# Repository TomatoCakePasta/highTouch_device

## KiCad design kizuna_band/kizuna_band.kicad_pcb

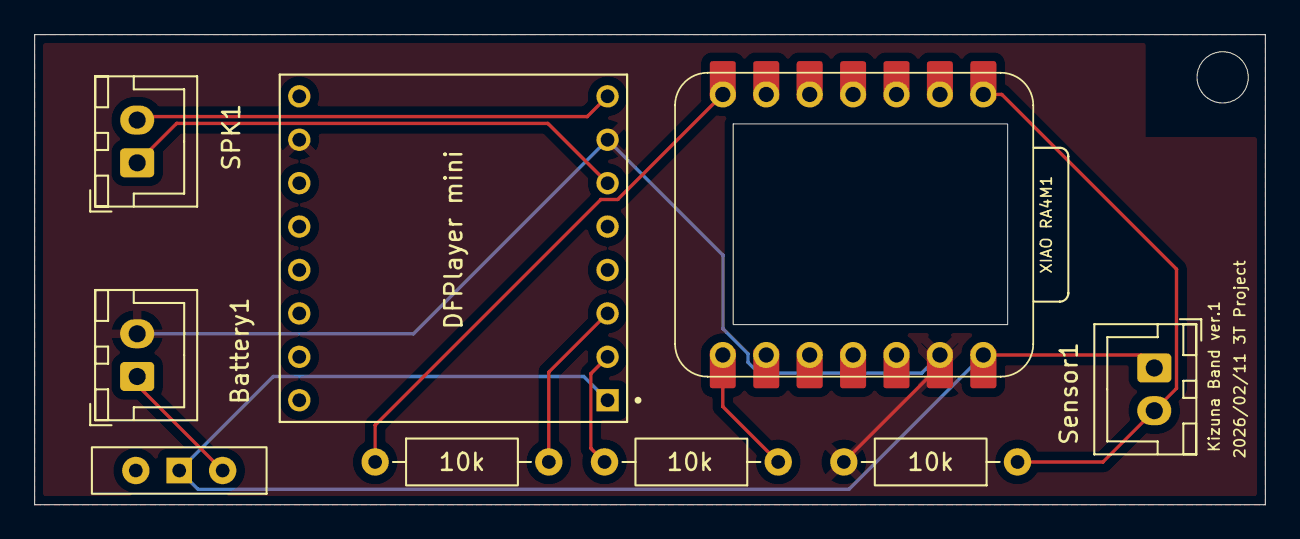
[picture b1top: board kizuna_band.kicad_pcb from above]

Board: 2 copper layers, 72.0 x 27.5 mm, 10 parts (0 on the bottom side), 10 nets.

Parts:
10k, 10k#2: 10k; R_Axial_DIN0207_L6.3mm_D2.5mm_P10.16mm_Horizontal
Battery1: Conn_Battery; JST_XH_B2B-XH-A_1x02_P2.50mm_Vertical
DFPlayer mini: DFR0299; MODULE_DFR0299
H1: MountingHole; MountingHole_3mm
R3: 10k; R_Axial_DIN0207_L6.3mm_D2.5mm_P10.16mm_Horizontal
SPK1: Conn_SPK; JST_XH_B2B-XH-A_1x02_P2.50mm_Vertical
SW1: SW_Battery; SW_Slide-03_Wuerth-WS-SLTV_10x2.5x6.4_P2.54mm
Sensor1: Conn_Seneosr; JST_XH_B2B-XH-A_1x02_P2.50mm_Vertical
XIAO RA4M1: XIAO-RA4M1-DIP; XIAO-R4-DIP

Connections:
5V: DFPlayer mini.1 (VCC), SW1.1 (B), Sensor1.1, XIAO RA4M1.14 (VBUS)
A0: R3.1, Sensor1.2, XIAO RA4M1.1 (P014_A0_D0)
GND: Battery1.2, DFPlayer mini.7 (GND), DFPlayer mini.10 (GND), R3.2, XIAO RA4M1.13 (GND)
unnamed: Battery1.1, SW1.2 (C)
unnamed: 10k.1, XIAO RA4M1.8 (P301_D7_SCL2_RXD2)
unnamed: 10k#2.1, XIAO RA4M1.7 (P302_D6_SDA2_TXD2)
unnamed: 10k.2, DFPlayer mini.2 (RX)
unnamed: 10k#2.2, DFPlayer mini.3 (TX)
SPK1 +: DFPlayer mini.6 (SPK1), SPK1.1
SPK2 -: DFPlayer mini.8 (SPK2), SPK1.2

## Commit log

2026-01-15 アジャイに変更
2026-01-15 グローバル変数を整理
2026-02-02 Seeeduinoのコードを追加
2026-02-06 RX, TXピン番号の修正
2026-02-11 プリント基板設計
2026-02-25 esp32のコード / ケースstlの追加
2026-02-25 ケーススナップフィット修正
2026-02-27 xiao esp32-c6のコードを実装
2026-02-28 add gitignore
2026-02-28 モード切り替え, 演奏モード追加
2026-03-16 ESP32C6_演奏モード追加
